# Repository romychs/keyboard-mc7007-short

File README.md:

# Клавиатура МС-7007 короткая

Клавиатура на клавишах Cherry-MX похожая на МС-7007. Без правого цифрового блока (74 клавиши).

Разрабатывалась для реплики компьютера "Электроника-КР04".

[Исходники в KiCAD v9](KiCAD)

[Готовые схемы](Export)

[Файлы для производства печатной платы](Gerbers/Keyboard-MC7007-Short-gerbers_v1.0.2.zip)

[Layout файл](Layout) для [Keyboard Layout Editor](https://www.keyboard-layout-editor.com/)

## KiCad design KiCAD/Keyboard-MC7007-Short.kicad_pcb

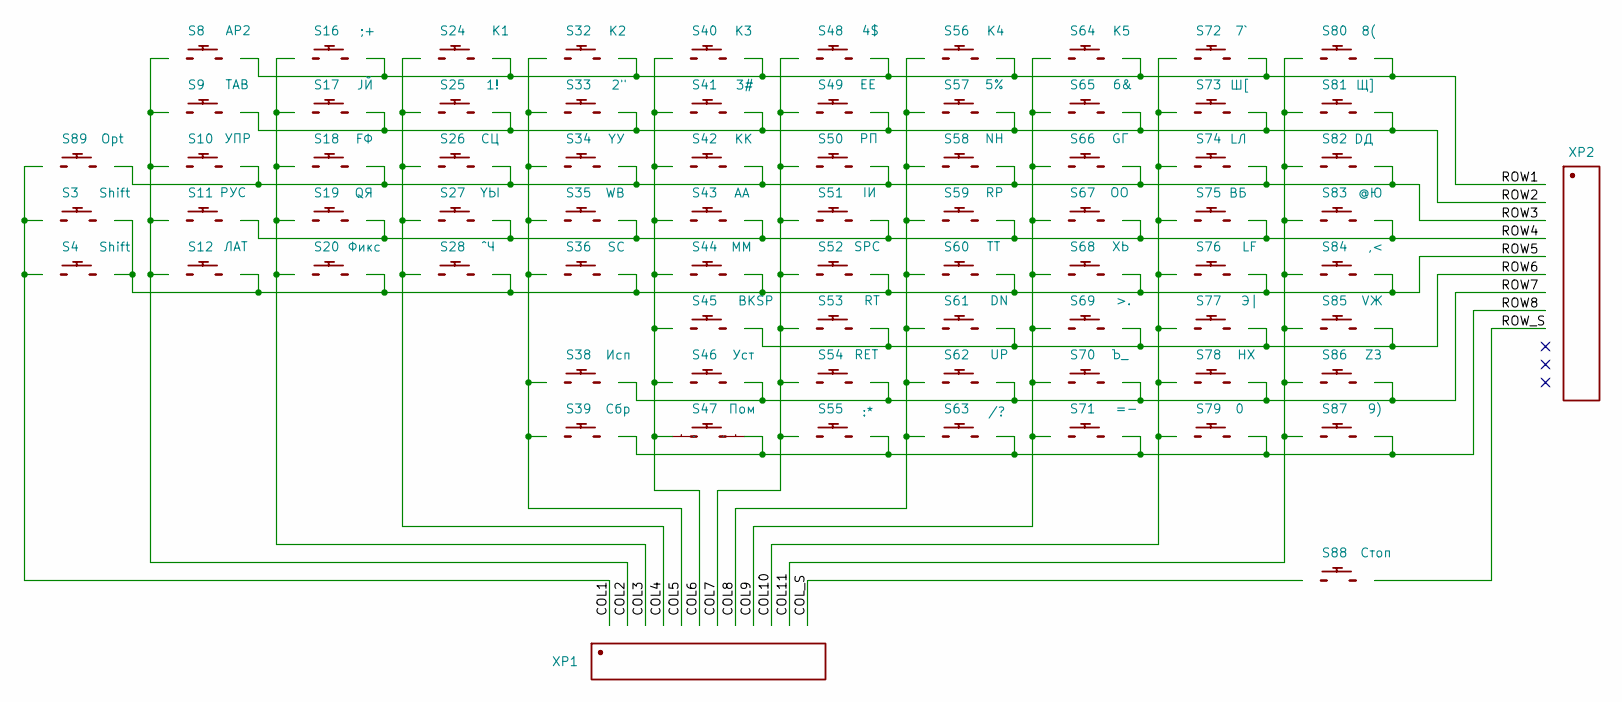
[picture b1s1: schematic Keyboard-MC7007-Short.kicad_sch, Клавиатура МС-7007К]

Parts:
S3, S4: Shift; CHERRY_MX
S8: AP2; CHERRY_MX
S9: TAB; CHERRY_MX
S10: УПР; CHERRY_MX
S11: РУС; CHERRY_MX
S12: ЛАТ; CHERRY_MX
S16: ;+; CHERRY_MX
S17: JЙ; CHERRY_MX
S18: FФ; CHERRY_MX
S19: QЯ; CHERRY_MX
S20: Фикс; CHERRY_MX
S24: K1; CHERRY_MX
S25: 1!; CHERRY_MX
S26: CЦ; CHERRY_MX
S27: YЫ; CHERRY_MX
S28: ^Ч; CHERRY_MX
S32: K2; CHERRY_MX
S33: 2"; CHERRY_MX
S34: YУ; CHERRY_MX
S35: WВ; CHERRY_MX
S36: SС; CHERRY_MX
S38: Исп; CHERRY_MX
S39: Сбр; CHERRY_MX
S40: K3; CHERRY_MX
S41: 3#; CHERRY_MX
S42: KК; CHERRY_MX
S43: АA; CHERRY_MX
S44: MМ; CHERRY_MX
S45: BKSP; CHERRY_MX
S46: Уст; CHERRY_MX
S47: Пом; CHERRY_MX
S48: 4$; CHERRY_MX
S49: EЕ; CHERRY_MX
S50: PП; CHERRY_MX
S51: IИ; CHERRY_MX
S52: SPC; CHERRY_MX
S53: RT; CHERRY_MX
S54: RET; CHERRY_MX
S55: :*; CHERRY_MX
S56: K4; CHERRY_MX
S57: 5%; CHERRY_MX
S58: NН; CHERRY_MX
S59: RР; CHERRY_MX
S60: TТ; CHERRY_MX
S61: DN; CHERRY_MX
S62: UP; CHERRY_MX
S63: /?; CHERRY_MX
S64: K5; CHERRY_MX
S65: 6&; CHERRY_MX
S66: GГ; CHERRY_MX
S67: OО; CHERRY_MX
S68: XЬ; CHERRY_MX
S69: >.; CHERRY_MX
S70: Ъ_; CHERRY_MX
S71: =-; CHERRY_MX
S72: 7`; CHERRY_MX
S73: Ш[; CHERRY_MX
S74: LЛ; CHERRY_MX
S75: BБ; CHERRY_MX
S76: LF; CHERRY_MX
S77: Э|; CHERRY_MX
S78: HХ; CHERRY_MX
S79: 0; CHERRY_MX
S80: 8(; CHERRY_MX
S81: Щ]; CHERRY_MX
S82: DД; CHERRY_MX
S83: @Ю; CHERRY_MX
S84: ,<; CHERRY_MX
S85: VЖ; CHERRY_MX
S86: ZЗ; CHERRY_MX
S87: 9); CHERRY_MX
S88: Стоп; CHERRY_MX
S89: Opt; CHERRY_MX
XP1: HDR-TH-12x1-2.54P; HDR-TH_12P-P2.54-V-M; Manufacturer Part PZ254-1-12-Z-8.5
XP2: PZ254-1-12-Z-8.5; HDR-TH_12P-P2.54-V-M; Manufacturer Part PZ254-1-12-Z-8.5

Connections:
/COL1: S3.S1 (1), S4.S1 (1), S89.S1 (1), XP1.1
/COL2: S8.S1 (1), S9.S1 (1), S10.S1 (1), S11.S1 (1), S12.S1 (1), XP1.2
/COL3: S16.S1 (1), S17.S1 (1), S18.S1 (1), S19.S1 (1), S20.S1 (1), XP1.3
/COL4: S24.S1 (1), S25.S1 (1), S26.S1 (1), S27.S1 (1), S28.S1 (1), XP1.4
/COL5: S32.S1 (1), S33.S1 (1), S34.S1 (1), S35.S1 (1), S36.S1 (1), S38.S1 (1), S39.S1 (1), XP1.5
/COL6: S40.S1 (1), S41.S1 (1), S42.S1 (1), S43.S1 (1), S44.S1 (1), S45.S1 (1), S46.S1 (1), S47.S1 (1), XP1.6
/COL7: S48.S1 (1), S49.S1 (1), S50.S1 (1), S51.S1 (1), S52.S1 (1), S53.S1 (1), S54.S1 (1), S55.S1 (1), XP1.7
/COL8: S56.S1 (1), S57.S1 (1), S58.S1 (1), S59.S1 (1), S60.S1 (1), S61.S1 (1), S62.S1 (1), S63.S1 (1), XP1.8
/COL9: S64.S1 (1), S65.S1 (1), S66.S1 (1), S67.S1 (1), S68.S1 (1), S69.S1 (1), S70.S1 (1), S71.S1 (1), XP1.9
/COL10: S72.S1 (1), S73.S1 (1), S74.S1 (1), S75.S1 (1), S76.S1 (1), S77.S1 (1), S78.S1 (1), S79.S1 (1), XP1.10
/COL11: S80.S1 (1), S81.S1 (1), S82.S1 (1), S83.S1 (1), S84.S1 (1), S85.S1 (1), S86.S1 (1), S87.S1 (1), XP1.11
/COL_S: S88.S1 (1), XP1.12
/ROW1: S8.S2 (2), S16.S2 (2), S24.S2 (2), S32.S2 (2), S40.S2 (2), S48.S2 (2), S56.S2 (2), S64.S2 (2), S72.S2 (2), S80.S2 (2), XP2.1
/ROW2: S9.S2 (2), S17.S2 (2), S25.S2 (2), S33.S2 (2), S41.S2 (2), S49.S2 (2), S57.S2 (2), S65.S2 (2), S73.S2 (2), S81.S2 (2), XP2.2
/ROW3: S10.S2 (2), S18.S2 (2), S26.S2 (2), S34.S2 (2), S42.S2 (2), S50.S2 (2), S58.S2 (2), S66.S2 (2), S74.S2 (2), S82.S2 (2), S89.S2 (2), XP2.3
/ROW4: S11.S2 (2), S19.S2 (2), S27.S2 (2), S35.S2 (2), S43.S2 (2), S51.S2 (2), S59.S2 (2), S67.S2 (2), S75.S2 (2), S83.S2 (2), XP2.4
/ROW5: S3.S2 (2), S4.S2 (2), S12.S2 (2), S20.S2 (2), S28.S2 (2), S36.S2 (2), S44.S2 (2), S52.S2 (2), S60.S2 (2), S68.S2 (2), S76.S2 (2), S84.S2 (2), XP2.5
/ROW6: S45.S2 (2), S53.S2 (2), S61.S2 (2), S69.S2 (2), S77.S2 (2), S85.S2 (2), XP2.6
/ROW7: S38.S2 (2), S46.S2 (2), S54.S2 (2), S62.S2 (2), S70.S2 (2), S78.S2 (2), S86.S2 (2), XP2.7
/ROW8: S39.S2 (2), S47.S2 (2), S55.S2 (2), S63.S2 (2), S71.S2 (2), S79.S2 (2), S87.S2 (2), XP2.8
/ROW_S: S88.S2 (2), XP2.9

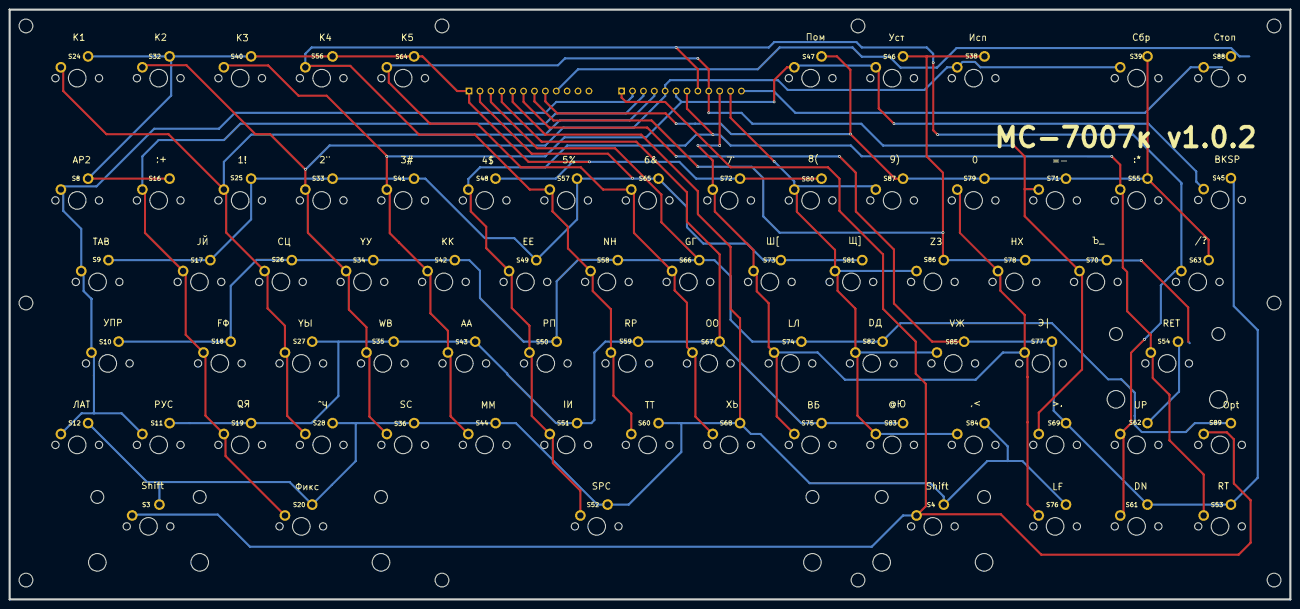
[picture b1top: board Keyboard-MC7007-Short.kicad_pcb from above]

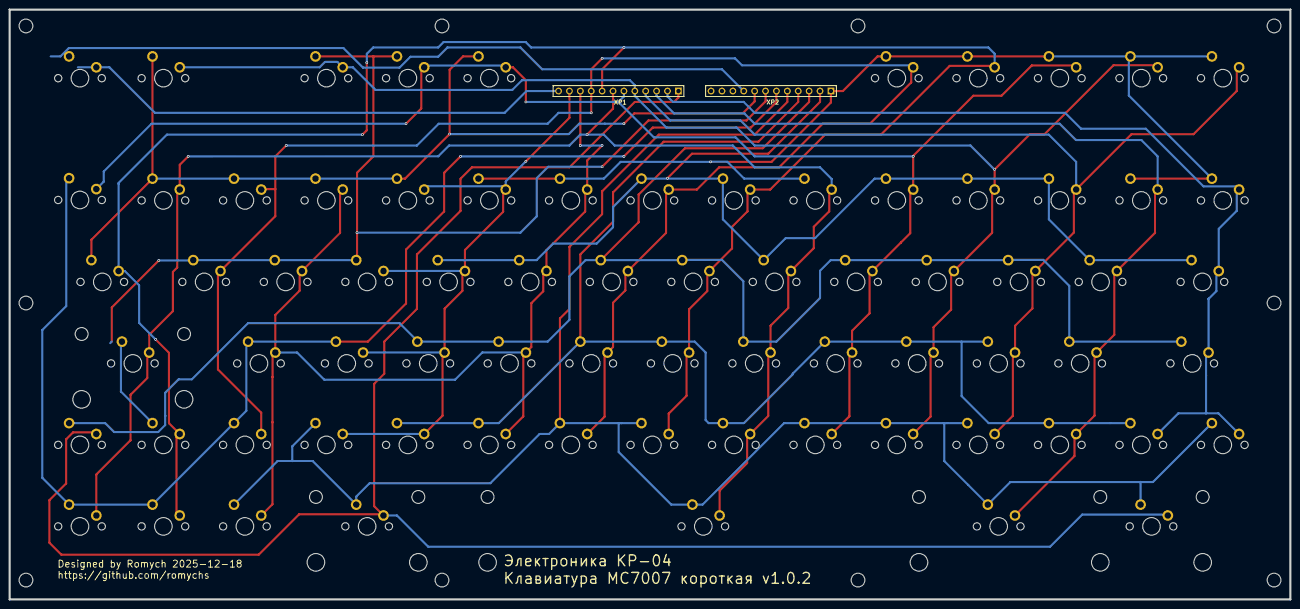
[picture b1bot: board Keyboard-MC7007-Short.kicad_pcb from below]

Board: 2 copper layers, 298.6 x 137.5 mm, 80 parts (3 on the bottom side), 21 nets.

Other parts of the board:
STAB_2, STAB_6, STAB_7: CHERRYMX STABILIZER 2U
STAB_5: MX1A STABILIZER 6.25U

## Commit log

2025-12-18 v1.0.2
